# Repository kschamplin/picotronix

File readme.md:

# Picotronix: Pico-based driver for Tektronix vector displays.

Picotronix is an adapter board that can interface with Tektronix 603/604 series vector displays,
and is capable of using the storage features if they are available.

It connects to the remote DB25 connector to provide all the inputs and controls, and can be interfaced
over usb for PC control or directly run it's own visuals.

It also has two ESP-01-compatible pin headers for IO expansions to meet specific application needs.

## Project Structure

Since this project is multi-domain (PC library, RP2040 Firmware, and KiCAD PCB),
the project is split up into respective subfolders. To facilitate communication between the Pico and
the PC, `Cap'n Proto` is used as a protocol exchange library generator.

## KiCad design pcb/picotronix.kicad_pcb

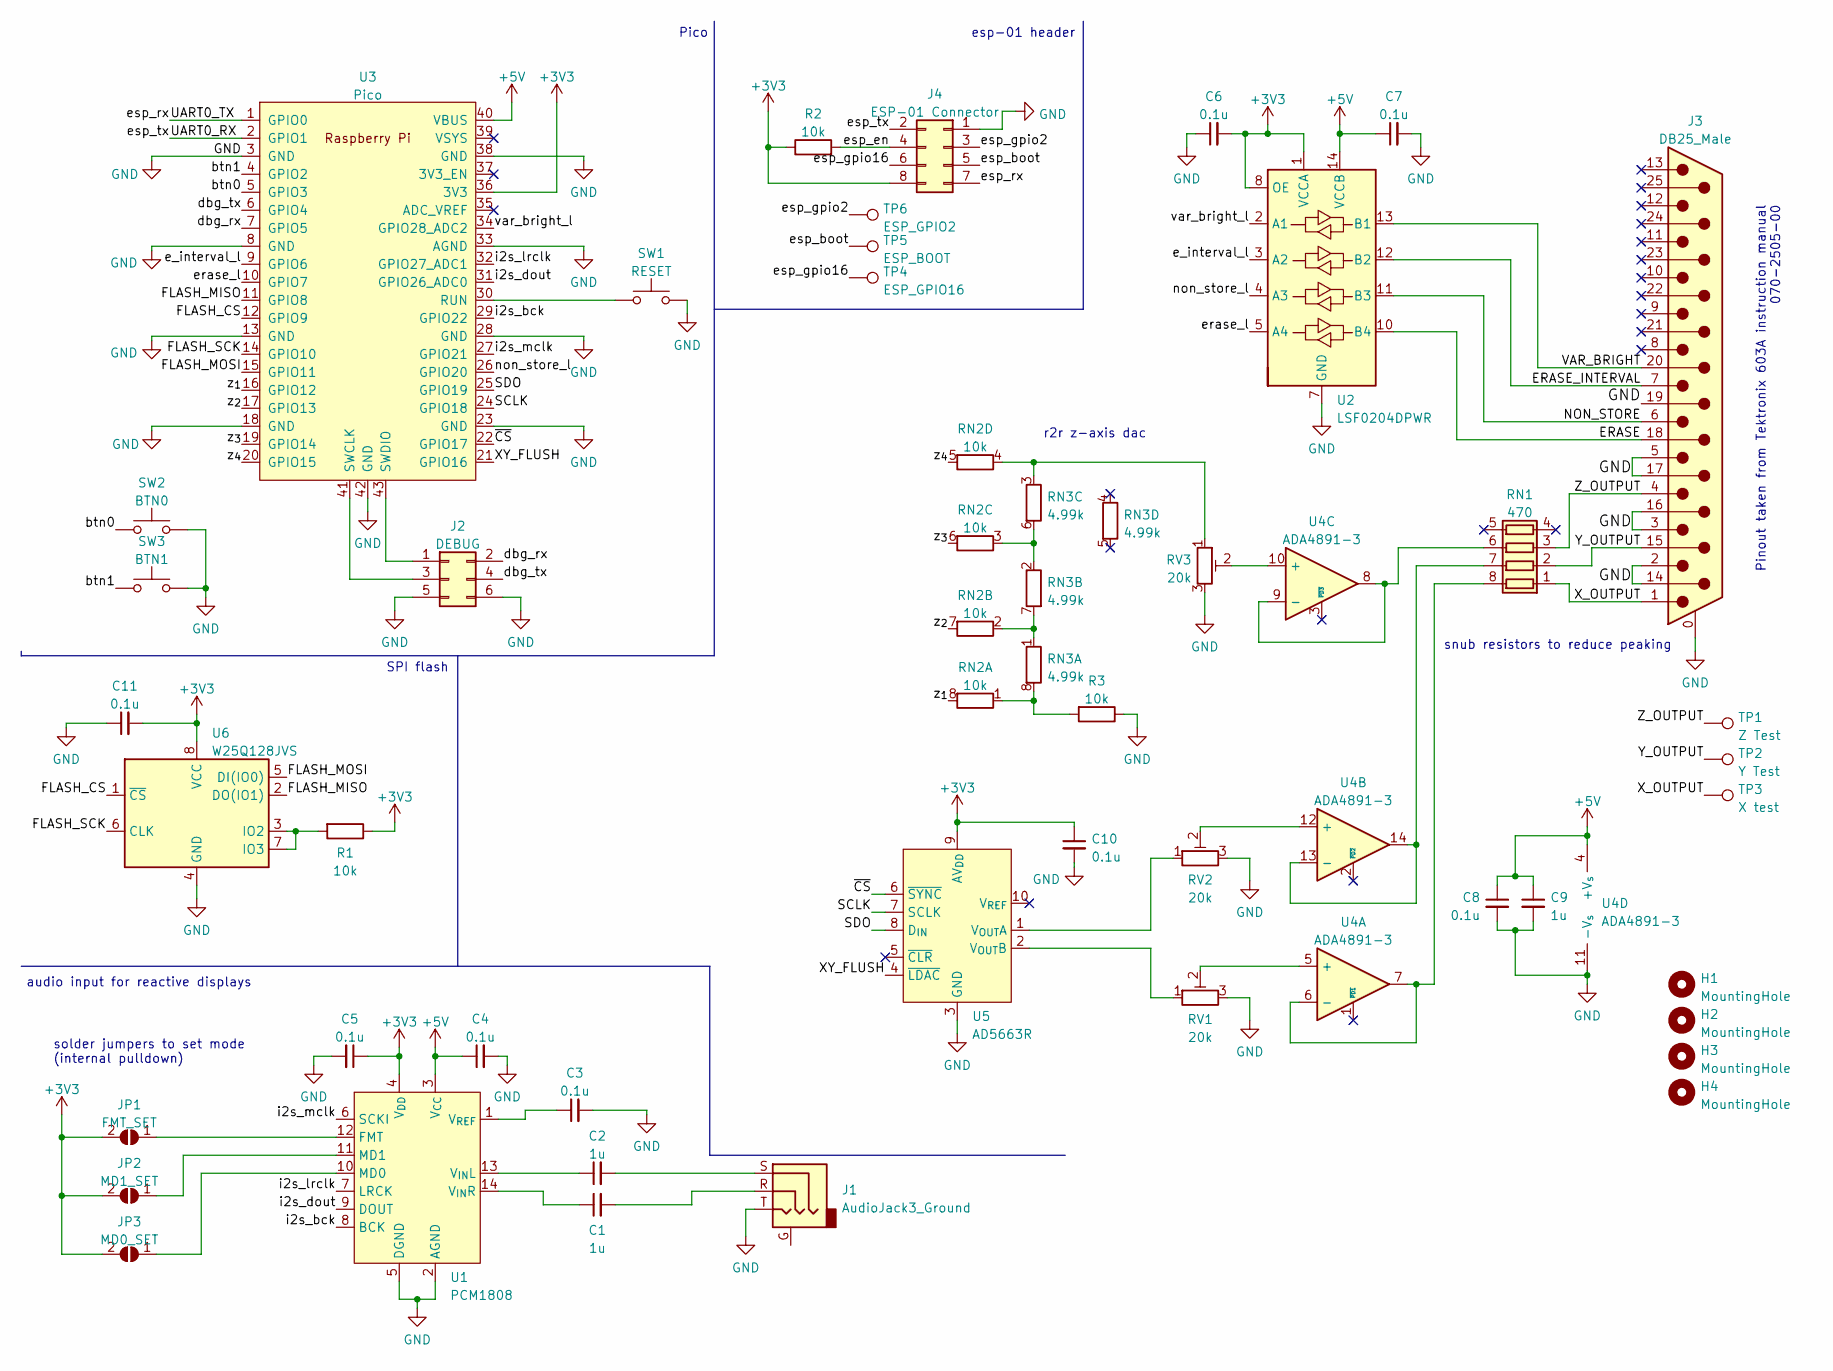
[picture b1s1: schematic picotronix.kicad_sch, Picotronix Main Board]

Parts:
C1, C2, C9: 1u; C_0603_1608Metric_Pad1.08x0.95mm_HandSolder; Digikey_PN 1276-1102-1-ND
C3, C4, C5, C6, C7, C8, C10, C11: 0.1u; C_0603_1608Metric_Pad1.08x0.95mm_HandSolder; Digikey_PN 1276-CL10B104KB8NNNLCT-ND
H1, H2, H3, H4: MountingHole; MountingHole_3.2mm_M3
J1: AudioJack3_Ground; Jack_3.5mm_CUI_SJ-3524-SMT_Horizontal; Digikey_PN CP-3524SJCT-ND
J2: DEBUG; PinHeader_2x03_P2.54mm_Vertical; Digikey_PN S2011EC-03-ND
J3: DB25_Male; DSUB-25_Male_Horizontal_P2.77x2.84mm_EdgePinOffset9.90mm_Ho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; Digikey_PN AE10982-ND
J4: ESP-01 Connector; PinSocket_2x04_P2.54mm_Vertical; Digikey_PN S7107-ND
JP1: FMT_SET; SolderJumper-2_P1.3mm_Open_TrianglePad1.0x1.5mm
JP2: MD1_SET; SolderJumper-2_P1.3mm_Open_TrianglePad1.0x1.5mm
JP3: MD0_SET; SolderJumper-2_P1.3mm_Open_TrianglePad1.0x1.5mm
R1, R2, R3: 10k; R_0603_1608Metric_Pad0.98x0.95mm_HandSolder; Digikey_PN RNCP0603FTD10K0CT-ND
RN1: 470; R_Array_Convex_4x1206; Digikey_PN CAY16-4700F4LFCT-ND
RN2: 10k; R_Array_Convex_4x1206; Digikey_PN CAY16-1002F4LFCT-ND
RN3: 4.99k; R_Array_Convex_4x1206; Digikey_PN CAY16-4991F4LFCT-ND
RV1, RV2, RV3: 20k; Potentiometer_Bourns_TC33X_Vertical; Digikey_PN TC33X-2-203ECT-ND
SW1: RESET; SW_SPST_TL3305A; Digikey_PN EG5353CT-ND
SW2: BTN0; SW_SPST_TL3305A; Digikey_PN EG5353CT-ND
SW3: BTN1; SW_SPST_TL3305A; Digikey_PN EG5353CT-ND
TP1: Z Test; TestPoint_Pad_D1.0mm
TP2: Y Test; TestPoint_Pad_D1.0mm
TP3: X test; TestPoint_Pad_D1.0mm
TP4: ESP_GPIO16; TestPoint_Pad_D1.0mm
TP5: ESP_BOOT; TestPoint_Pad_D1.0mm
TP6: ESP_GPIO2; TestPoint_Pad_D1.0mm
U1: PCM1808; TSSOP-14_4.4x5mm_P0.65mm; Digikey_PN 296-19773-ND
U2: LSF0204DPWR; TSSOP-14_4.4x5mm_P0.65mm; Digikey_PN 296-40400-1-ND
U3: Pico; RPi_Pico_SMD_TH; Digikey_PN 2648-SC0915CT-ND
U4: ADA4891-3; TSSOP-14_4.4x5mm_P0.65mm; Digikey_PN ADA4891-3WARUZ-R7CT-ND
U5: AD5663R; MSOP-10_3x3mm_P0.5mm; Digikey_PN 505-AD5623RBRMZ-5-ND
U6: W25Q128JVS; SOIC-8_5.23x5.23mm_P1.27mm; Digikey_PN W25Q128JVSIM-ND

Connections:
+3V3: C5.1, C6.2, C10.1, C11.2, J4.8, JP1.2 (B), JP2.2 (B), JP3.2 (B), R1.1, R2.1, U1.4 (V_{DD}), U2.1 (VCCA), U2.8 (OE), U3.36 (3V3), U5.9 (AV_{DD}), U6.8 (VCC)
+5V: C4.1, C7.1, C8.1, C9.1, U1.3 (V_{CC}), U2.14 (VCCB), U3.40 (VBUS), U4.4 (+V_{s})
/ERASE: J3.18, U2.10 (B4)
/ERASE_INTERVAL: J3.7, U2.12 (B2)
/FLASH_CS: U3.12 (GPIO9), U6.1 (~CS)
/FLASH_MISO: U3.11 (GPIO8), U6.2 (DO(IO1))
/FLASH_MOSI: U3.15 (GPIO11), U6.5 (DI(IO0))
/FLASH_SCK: U3.14 (GPIO10), U6.6 (CLK)
/NON_STORE: J3.6, U2.11 (B3)
/SCLK: U3.24 (GPIO18), U5.7 (SCLK)
/SDO: U3.25 (GPIO19), U5.8 (D_{IN})
/UART0_RX: J4.2, U3.2 (GPIO1)
/UART0_TX: J4.7, U3.1 (GPIO0)
/VAR_BRIGHT: J3.20, U2.13 (B1)
/XY_FLUSH: U3.21 (GPIO16), U5.4 (~LDAC)
/X_OUTPUT: J3.1, RN1.1 (R1.1), TP3.1
/Y_OUTPUT: J3.15, RN1.2 (R2.1), TP2.1
/Z_OUTPUT: J3.4, RN1.3 (R3.1), TP1.1
/btn0: SW2.1, U3.5 (GPIO3)
/btn1: SW3.1, U3.4 (GPIO2)
/dbg_rx: J2.2, U3.7 (GPIO5)
/dbg_tx: J2.4, U3.6 (GPIO4)
/e_interval_l: U2.3 (A2), U3.9 (GPIO6)
/erase_l: U2.5 (A4), U3.10 (GPIO7)
/esp_boot: J4.5, TP5.1
/esp_en: J4.4, R2.2
/esp_gpio2: J4.3, TP6.1
/esp_gpio16: J4.6, TP4.1
/i2s_bck: U1.8 (BCK), U3.29 (GPIO22)
/i2s_dout: U1.9 (DOUT), U3.31 (GPIO26_ADC0)
/i2s_lrclk: U1.7 (LRCK), U3.32 (GPIO27_ADC1)
/i2s_mclk: U1.6 (SCKI), U3.27 (GPIO21)
/non_store_l: U2.4 (A3), U3.26 (GPIO20)
/var_bright_l: U2.2 (A1), U3.34 (GPIO28_ADC2)
/z_{1}: RN2.8 (R1.2), U3.16 (GPIO12)
/z_{2}: RN2.7 (R2.2), U3.17 (GPIO13)
/z_{3}: RN2.6 (R3.2), U3.19 (GPIO14)
/z_{4}: RN2.5 (R4.2), U3.20 (GPIO15)
/~CS: U3.22 (GPIO17), U5.6 (~SYNC)
GND: C3.2, C4.2, C5.2, C6.1, C7.2, C8.2, C9.2, C10.2, C11.1, J1.T, J2.5, J2.6, J3.0 (PAD), J3.2, J3.3, J3.5, J3.14, J3.16, J3.17, J3.19, J4.1, R3.1, RV1.3, RV2.3, RV3.3, SW1.2, SW2.2, SW3.2, U1.2 (AGND), U1.5 (DGND), U2.7 (GND), U3.3 (GND), U3.8 (GND), U3.13 (GND), U3.18 (GND), U3.23 (GND), U3.28 (GND), U3.33 (AGND), U3.38 (GND), U3.42 (GND), U4.11 (-V_{s}), U5.3 (GND), U6.4 (GND)
unnamed: C1.1, U1.14 (V_{IN}R)
unnamed: C1.2, J1.R
unnamed: C2.1, U1.13 (V_{IN}L)
unnamed: C2.2, J1.S
unnamed: C3.1, U1.1 (V_{REF})
unnamed: J2.1, U3.43 (SWDIO)
unnamed: J2.3, U3.41 (SWCLK)
unnamed: JP1.1 (A), U1.12 (FMT)
unnamed: JP2.1 (A), U1.11 (MD1)
unnamed: JP3.1 (A), U1.10 (MD0)
unnamed: R1.2, U6.3 (IO2), U6.7 (IO3)
unnamed: R3.2, RN2.1 (R1.1), RN3.8 (R1.2)
unnamed: RN1.6 (R3.2), U4.8, U4.9 (-)
unnamed: RN1.7 (R2.2), U4.13 (-), U4.14
unnamed: RN1.8 (R1.2), U4.6 (-), U4.7
unnamed: RN2.2 (R2.1), RN3.1 (R1.1), RN3.7 (R2.2)
unnamed: RN2.3 (R3.1), RN3.2 (R2.1), RN3.6 (R3.2)
unnamed: RN2.4 (R4.1), RN3.3 (R3.1), RV3.1
unnamed: RV1.1, U5.2 (V_{OUT}B)
unnamed: RV1.2, U4.5 (+)
unnamed: RV2.1, U5.1 (V_{OUT}A)
unnamed: RV2.2, U4.12 (+)
unnamed: RV3.2, U4.10 (+)
unnamed: SW1.1, U3.30 (RUN)

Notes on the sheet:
Pico
solder jumpers to set mode (internal pulldown)
esp-01 header
r2r z-axis dac
audio input for reactive displays
Pinout taken from Tektronix 603A instruction manual 070-2505-00
snub resistors to reduce peaking
SPI flash

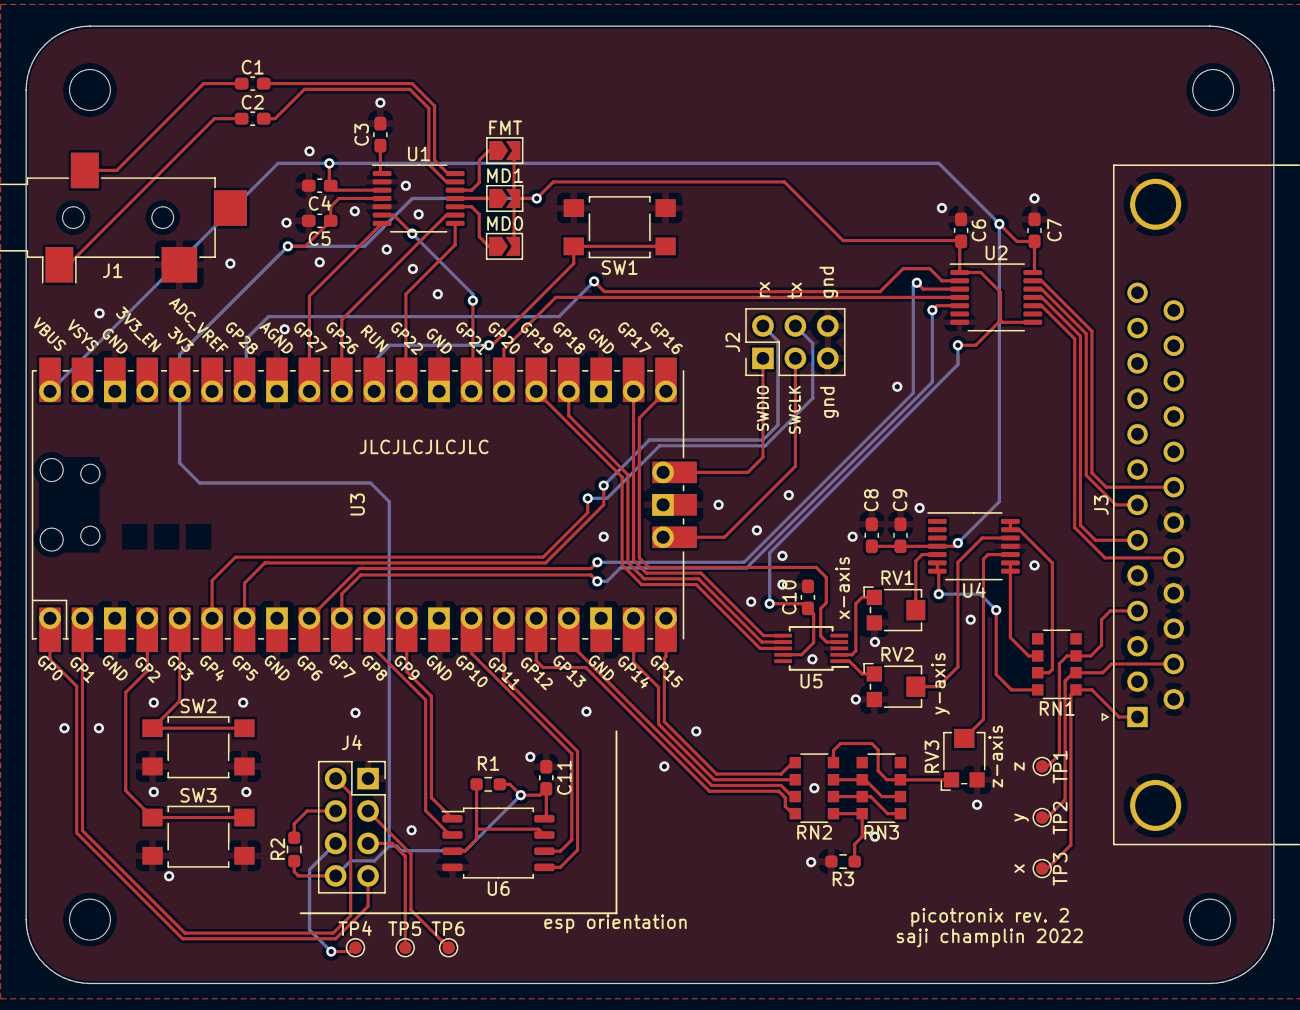
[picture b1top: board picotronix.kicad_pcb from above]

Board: 2 copper layers, 97.8 x 75.0 mm, 46 parts (0 on the bottom side), 64 nets.

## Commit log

2022-03-13 finish rev 1
2022-03-16 move pcb to subdirectory
2022-03-17 added firmware
2022-03-19 revised
2022-03-19 added pico sdk and test programs
2022-03-19 update pcb
2022-03-24 pcb rev2 routed
2022-03-27 pcb final revision
2022-03-29 minor revisions to board and schematic (mostly cleanup)
2022-04-01 some pcb tweaks (ordered this commit for rev 1)
2022-04-01 added vector game firmware
2022-12-16 added software tool
2022-12-16 make window
